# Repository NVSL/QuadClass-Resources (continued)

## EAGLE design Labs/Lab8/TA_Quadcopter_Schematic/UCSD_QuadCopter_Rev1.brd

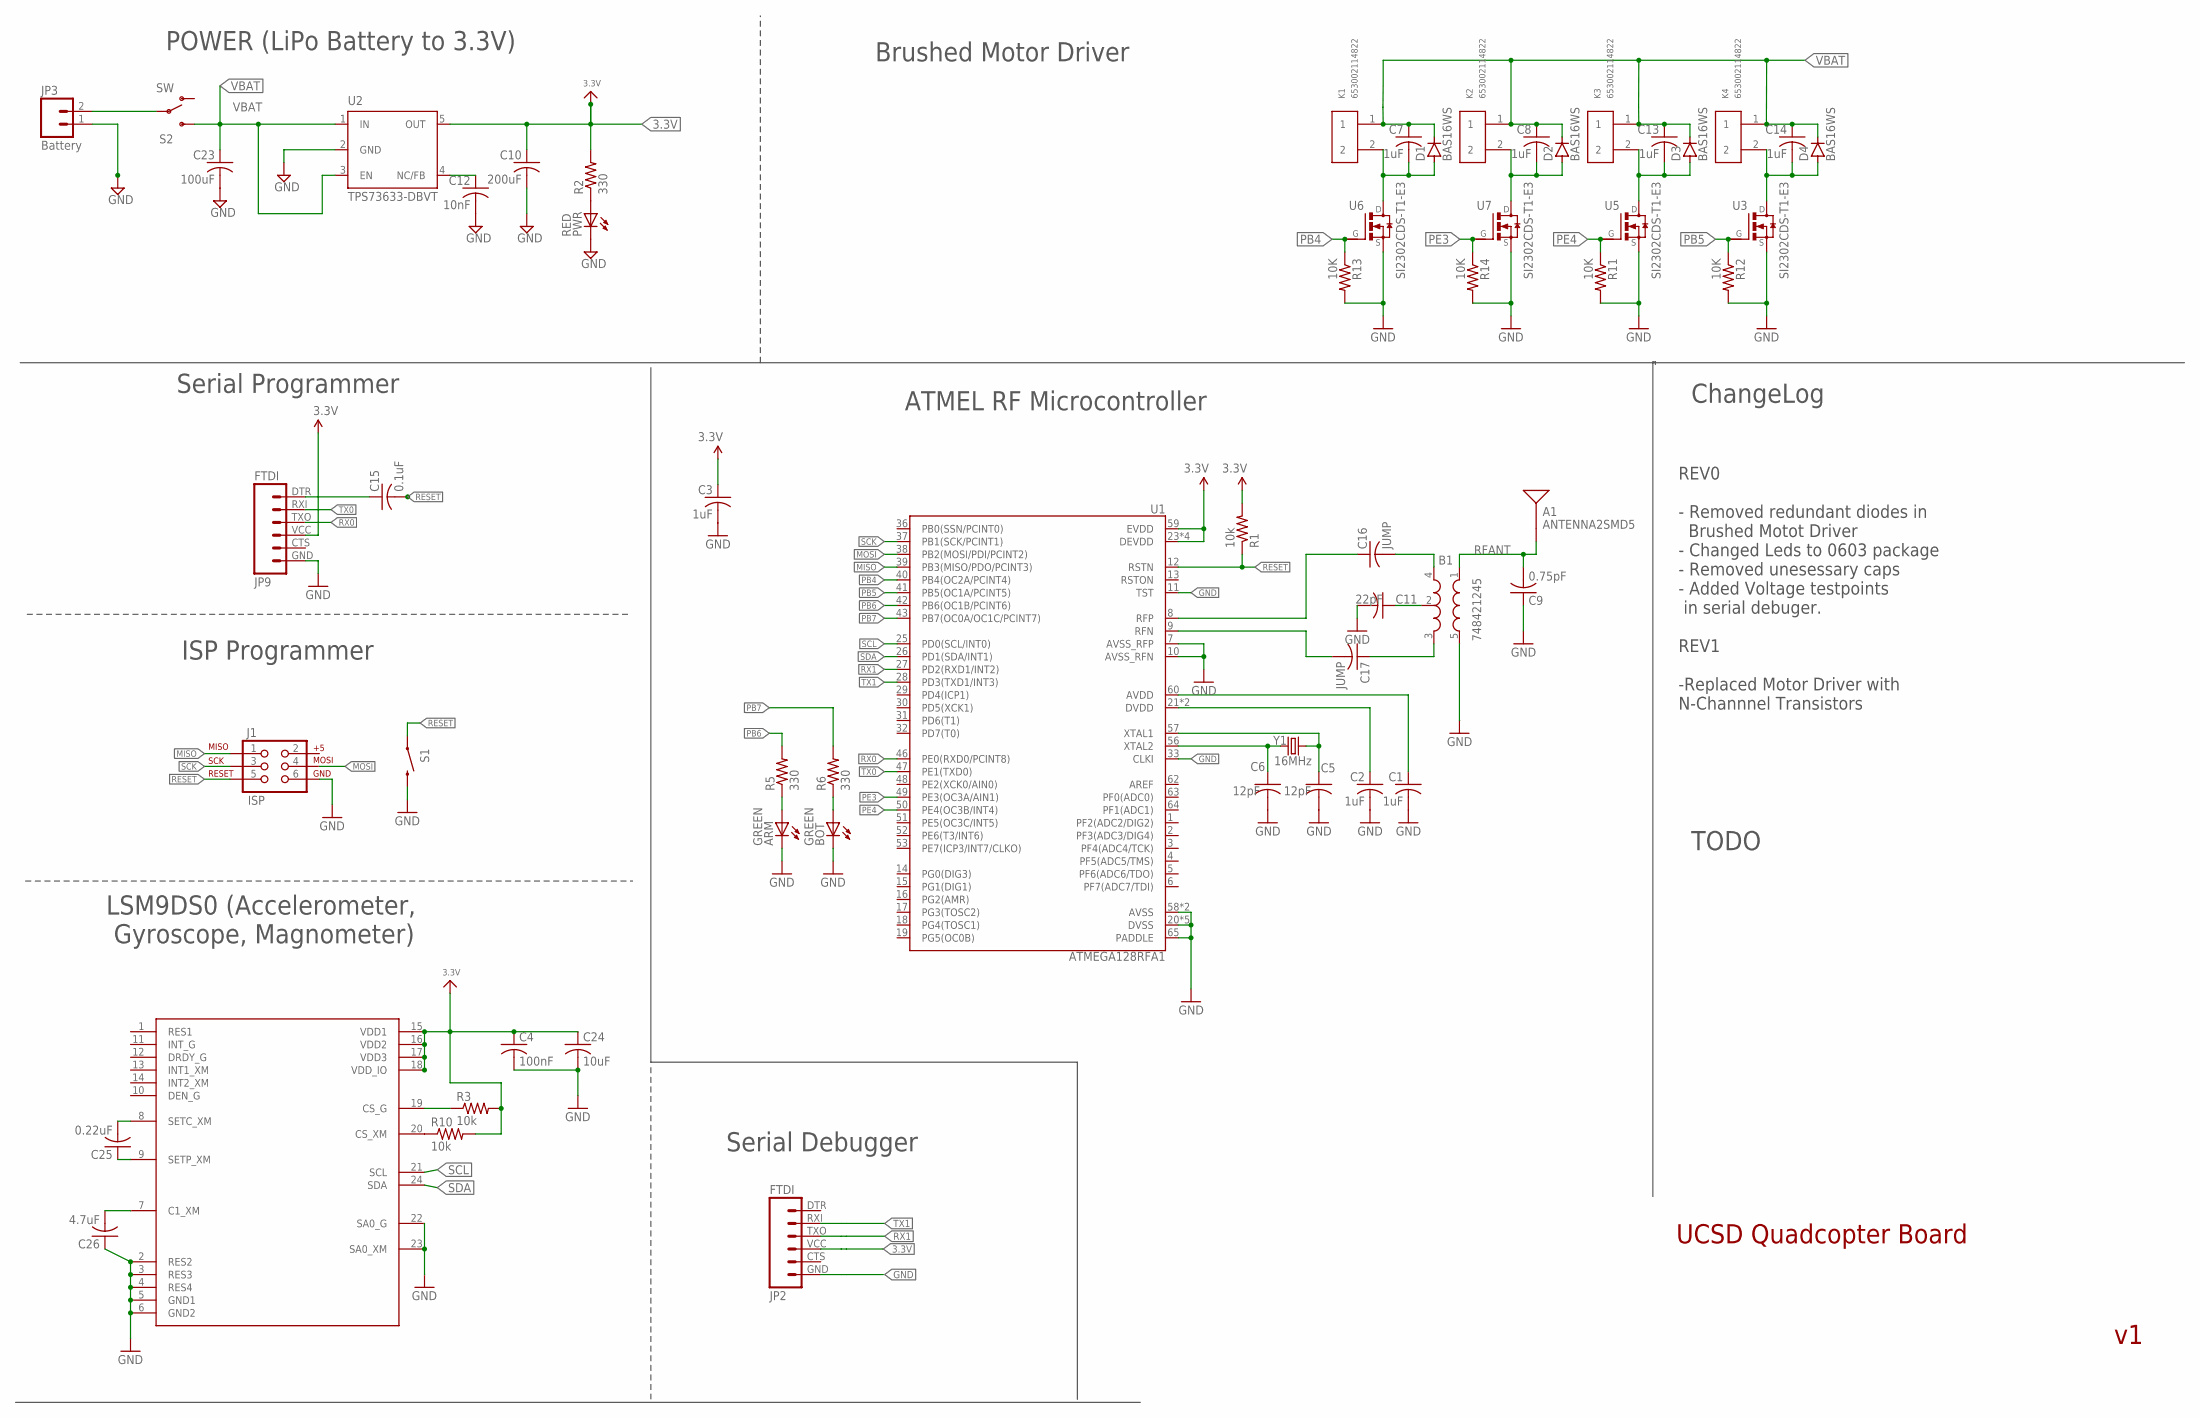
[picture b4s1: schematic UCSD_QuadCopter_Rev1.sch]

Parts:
A1: ANTENNA2SMD5; ANTENNA-CHIP5
ARM: GREEN; CHIP-LED0805
B1: 748421245; BALUN
BOT: GREEN; CHIP-LED0805
C1, C2, C3, C7, C8, C13, C14: 1uF; C0805
C4: 100nF; C0805
C5, C6: 12pF; C0805
C9: 0.75pF; C0805
C10: 200uF; C0805
C11: 22pF; C0805
C12: 10nF; C0805
C15: 0.1uF; C0805
C16, C17: JUMP; C0805
C23: 100uF; C0805
C24: 10uF; C0805
C25: 0.22uF; C0805
C26: 4.7uF; C0805
D1, D2, D3, D4: BAS16WS; SOD323_ST
J1: ISP; 2X3-NS
JP2, JP9: FTDI; FTDI_BASIC
JP3: Battery; 1X02
K1, K2, K3, K4: 653002114822
PWR: RED; CHIP-LED0805
R1, R3, R10: 10k; R0805
R2, R5, R6: 330; R0805
R11, R12, R13, R14: 10K; R0805
S1: SWITCH-MOMENTARY-2SMD; TACTILE_SWITCH_SMD
S2: SW; SWITCH-SPDT
U1: ATMEGA128RFA1; QFN-64
U2: TPS73633-DBVT; SOT23-DBV
U3, U5, U6, U7: SI2302CDS-T1-E3; SOT95P237X112-3N
U4: LSM9DS0; LGA-24
Y1: 16MHz; CRYSTAL-SMD-5X3

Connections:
3.3V: C3.1, C4.1, C10.1, C24.1, JP2.VCC (4), JP9.VCC (4), R1.2, R2.2, R3.2, R10.2, U1.23 (DEVDD), U1.34 (DEVDD), U1.44 (DEVDD), U1.54 (DEVDD), U1.59 (EVDD), U2.5 (OUT), U4.15 (VDD1), U4.16 (VDD2), U4.17 (VDD3), U4.18 (VDD_IO)
AVDD: C1.1, U1.60 (AVDD)
DTR: C15.1, JP9.DTR (1)
DVDD: C2.1, U1.21 (DVDD), U1.22 (DVDD)
GND: ARM.C, B1.5 (GND), BOT.C, C1.2, C2.2, C3.2, C4.2, C5.2, C6.2, C9.1, C10.2, C11.2, C12.2, C23.2, C24.2, C26.1, J1.6, JP2.GND (6), JP3.1, JP9.GND (6), PWR.C, R11.2, R12.2, R13.2, R14.2, S1.3 (2), U1.7 (AVSS_RFP), U1.10 (AVSS_RFN), U1.11 (TST), U1.20 (DVSS), U1.24 (DVSS), U1.33 (CLKI), U1.35 (DVSS), U1.45 (DVSS), U1.55 (DVSS), U1.58 (AVSS), U1.61 (AVSS), U1.65 (PADDLE), U2.2 (GND), U3.2 (S), U4.2 (RES2), U4.3 (RES3), U4.4 (RES4), U4.5 (GND1), U4.6 (GND2), U4.22 (SA0_G), U4.23 (SA0_XM), U5.2 (S), U6.2 (S), U7.2 (S)
MISO: J1.1, U1.39 (PB3(MISO/PDO/PCINT3))
MOSI: J1.4, U1.38 (PB2(MOSI/PDI/PCINT2))
unnamed: C12.1, U2.4 (NC/FB)
unnamed: PWR.A, R2.1
unnamed: C5.1, U1.57 (XTAL1), Y1.3 (2)
unnamed: C6.1, U1.56 (XTAL2), Y1.1
unnamed: B1.2 (GND), C11.1
unnamed: ARM.A, R5.1
unnamed: B1.4 (OUT1), C16.2
unnamed: B1.3 (OUT2), C17.1
unnamed: BOT.A, R6.1
unnamed: JP3.2, S2.2
unnamed: C26.2, U4.7 (C1_XM)
unnamed: C25.2, U4.8 (SETC_XM)
unnamed: C25.1, U4.9 (SETP_XM)
unnamed: R3.1, U4.19 (CS_G)
unnamed: R10.1, U4.20 (CS_XM)
unnamed: C7.2, D1.A, K1.2, U6.3 (D)
unnamed: C8.2, D2.A, K2.2, U7.3 (D)
unnamed: C13.2, D3.A, K3.2, U5.3 (D)
unnamed: C14.2, D4.A, K4.2, U3.3 (D)
PB4: R13.1, U1.40 (PB4(OC2A/PCINT4)), U6.1 (G)
PB5: R12.1, U1.41 (PB5(OC1A/PCINT5)), U3.1 (G)
PB6: R5.2, U1.42 (PB6(OC1B/PCINT6))
PB7: R6.2, U1.43 (PB7(OC0A/OC1C/PCINT7))
PE3: R14.1, U1.49 (PE3(OC3A/AIN1)), U7.1 (G)
PE4: R11.1, U1.50 (PE4(OC3B/INT4)), U5.1 (G)
RESET: C15.2, J1.5, R1.1, S1.1, U1.12 (RSTN)
RFANT: A1.FEED, B1.1 (IN), C9.2
RFN: C17.2, U1.9 (RFN)
RFP: C16.1, U1.8 (RFP)
RX0: JP9.TXO (3), U1.46 (PE0(RXD0/PCINT8))
RX1: JP2.TXO (3), U1.27 (PD2(RXD1/INT2))
SCK: J1.3, U1.37 (PB1(SCK/PCINT1))
SCL: U1.25 (PD0(SCL/INT0)), U4.21 (SCL)
SDA: U1.26 (PD1(SDA/INT1)), U4.24 (SDA)
TX0: JP9.RXI (2), U1.47 (PE1(TXD0))
TX1: JP2.RXI (2), U1.28 (PD3(TXD1/INT3))
VBAT: C7.1, C8.1, C13.1, C14.1, C23.1, D1.C, D2.C, D3.C, D4.C, K1.1, K2.1, K3.1, K4.1, S2.3 (S), U2.1 (IN), U2.3 (EN)

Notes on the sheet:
LSM9DS0 (Accelerometer, Gyroscope, Magnometer)
POWER (LiPo Battery to 3.3V)
Brushed Motor Driver
UCSD Quadcopter Board
Serial Programmer
ISP Programmer
Serial Debugger
ATMEL RF Microcontroller
ChangeLog
REV0 - Removed redundant diodes in Brushed Motot Driver - Changed Leds to 0603 package - Removed unesessary caps - Added Voltage testpoints in serial debuger. REV1 -Replaced Motor Driver with N-Channnel Transistors
TODO

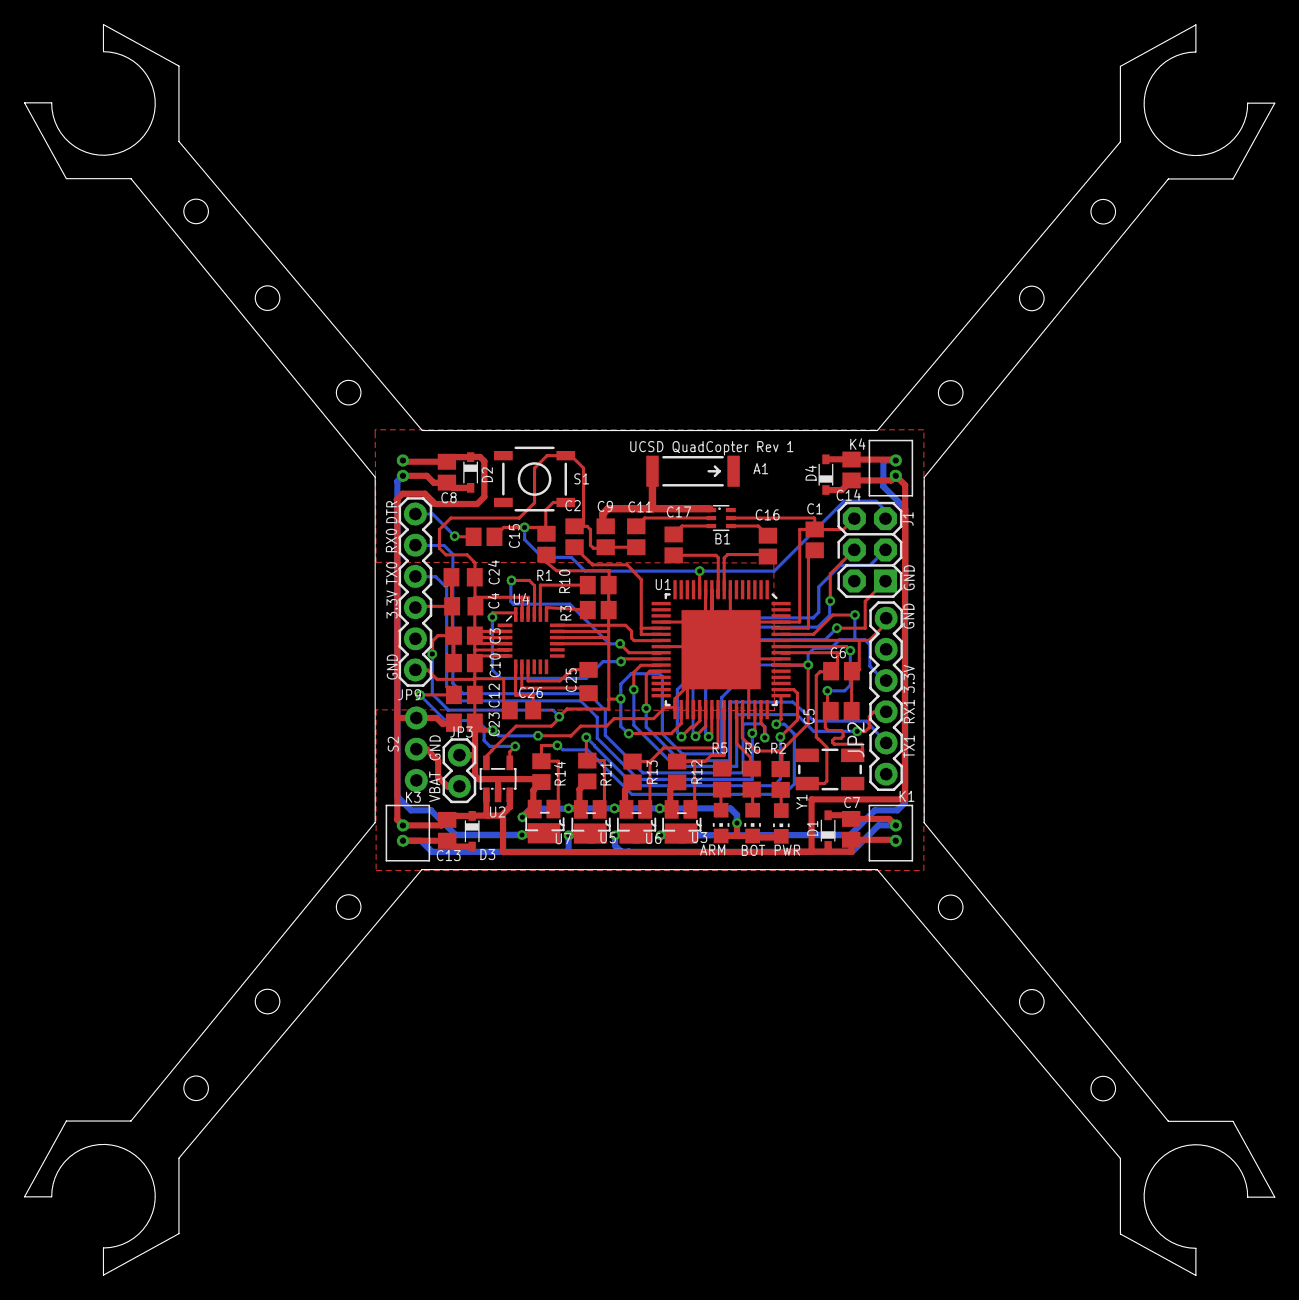
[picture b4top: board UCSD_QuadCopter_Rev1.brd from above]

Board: 2 copper layers, 101.8 x 101.9 mm, 58 parts (1 on the bottom side), 44 nets.

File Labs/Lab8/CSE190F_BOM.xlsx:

Quadcopter BOM
PART NUMBER | NAME | DESCRIPTION | Price Each
INTEGRATED CIRCUITS
ATMEGA128RFA1-ZUR00DKR-ND | ATMEGA128RFA1 | IC AVR MCU 2.4GHZ XCEIVER 64QFN | 10.31
497-13902-1-ND | LSM9DS0 | IC 3D acc; 3D gyro; 3D mag | 9.8699999999999992
LP3985IM5X-3.0/NOPBCT-ND | LP3985-3.0V | IC REG LDO 3V 0.15A SOT23-5 | 0.62
ANT-2.45-CHPCT-ND | ANTENNA | ANT 2.4GHZ 802.11 BLUETOOTH SMD | 3.16
732-2230-6-ND | BALUN Antenna Filter | BALUN EMBER351 & 357 0805 SMD | 2.63
SI2302CDS-T1-E3CT-ND | Mosfet N-Channel | MOSFET N-CH 20V 2.6A SOT-23 | 0.47
BAS16WS-E3-08CT-ND | Diode | DIODE GEN PURP 75V 250MA SOD323 | 0.23
535-9122-1-ND | Crystal | Crystal 16.0000MHz 20ppm 18pF 50 Ohm -20°C - 70°C Surface Mount 4-SMD, No Lead 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 | 1.04
LEDS
160-1412-1-ND | RED | LED RED ORANGE CLEAR 0805 SMD | 0.5
160-1887-1-ND | GREEN | LED GREEN CLEAR 0805 SMD | 0.55000000000000004
160-1887-1-ND | GREEN | LED GREEN CLEAR 0805 SMD | 0.55000000000000004
160-1416-1-ND | YELLOW | LED YELLOW CLEAR 0805 SMD | 0.37
160-1413-1-ND | ORANGE | LED YELLOW ORANGE CLEAR 0805 SMD | 0.32
160-1579-1-ND | BLUE | LED BLUE CLEAR 0805 SMD | 0.39
CAPACITORS
490-5531-1-ND | 12pF | CAP CER 12PF 250V 5% NP0 0805 | 0.28999999999999998
490-5534-1-ND | 22pF | CAP CER 22PF 250V 5% NP0 0805 | 0.28999999999999998
490-8295-1-ND | 0.01uF/10000PF | CAP CER 10000PF 50V 1% NP0 0805 | 0.65
490-1666-1-ND | 0.1uF/100nF | CAP CER 0.1UF 50V 10% X7R 0805 | 0.18
490-1670-1-ND | 0.22uF | CAP CER 0.22UF 50V 10% X7R 0805 | 0.25
1276-2702-1-ND | 0.75pF | CAP CER 0.75PF 50V NP0 0805 | 0.1
490-4736-1-ND | 1uF | CAP CER 1UF 50V 10% X7R 0805 | 0.45
490-3335-1-ND | 4.7uF | CAP CER 4.7UF 25V 10% X5R 0805 | 0.28999999999999998
490-5523-1-ND | 10uF | CAP CER 10UF 25V 10% X5R 0805 | 0.35
718-1607-1-ND | 100uF | CAP TANT 100UF 6.3V 20% 0805 | 2.0499999999999998
RESISTORS
311-10KARCT-ND | 10K Ohms | RES SMD 10K OHM 5% 1/8W 0805 | 0.1
311-270ARCT-ND | 270 Ohms | RES SMD 270 OHM 5% 1/8W 0805 | 0.1
311-680ARCT-ND | 680 Ohms | RES SMD 680 OHM 5% 1/8W 0805 | 0.1
311-100ARCT-ND | 100 Ohms | RES SMD 100 OHM 5% 1/8W 0805 | 0.1
311-30ARCT-ND | 30 Ohms | RES SMD 33 OHM 5% 1/8W 0805 | 0.1
311-0.0ARCT-ND | 0.0 Ohms | RES SMD 0.0 OHM JUMPER 1/8W 0805 | 0.1
311-330ARCT-ND | 330 Ohms | RES SMD 330 OHM 5% 1/8W 0805 | 0.1
SWITCHES
CKN9104CT-ND | Momentary Switch | SWITCH TACTILE SPST-NO 0.05A 12V | 0.65
https://www.sparkfun.com/products/9609 | Power Switch | SPDT Slide Switch | 0.75
CONECTORS
WM8344-ND | Crimp Terminal | CONN TERM MALE 24-28AWG TIN | 0.34
WM8347-ND | Plastic Connector | CONN PLUG 2POS 2MM WIRE TO WIRE | 0.37
(MOTORS, PROPELLER, BATTERY...)
http://www.amazon.com/AVAWO-Hubsan-H107C-Quadcopter-Velcro/d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 | Quad Misc | Hubsan Crash Pack | 26.99
Controller BOM
PART NUMBER | NAME | DESCRIPTION | Price Each
PARTS
CP3-1000-ND | Battery Plug | CONN 2.1MM FEMALE PLUG 5.5MM OUT | 1.36
BC4AAW-ND | AA Battery Holder | HOLDER BATT 4-AA CELLS WIRE LDS | 1.51
http://www.hobbyking.com/hobbyking/store/uh_viewItem.asp?idP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 | Gimble (L) | Gimbal Left | 4.71
http://www.hobbyking.com/hobbyking/store/uh_viewItem.asp?idP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 | Gimble (R) | Gimble Right | 4.76
https://www.sparkfun.com/products/11197 | Breakout Board | 128RFA1 board | 49.95
https://www.sparkfun.com/products/9067 | LCD | 3.3V Serial LCD | 24.95
S7005-ND | 1x7 female headers | Connector Header 7 Position 0.100" (2.54mm) Tin Through Hole | 0.78
S7006-ND | 1x8 female headers | Connector Header 8 Position 0.100" (2.54mm) Tin Through Hole | 0.86
S7004-ND | 1x6 female headers | Connector Header 6 Position 0.100" (2.54mm) Tin Through Hole | 0.68
929835E-01-36-ND | 1x6 right angle header | CONN HEADER .100 SNGL R/A 36POS | 1.88
CP-002A-ND | Barrel jack accepter | CONN POWER JACK 2.1MM | 0.93
https://www.sparkfun.com/products/11301 | USB mini cables | USB 2.0 type A to Mini-B 5-pin cable | 3.95
N107-ND | AA batteries | BATTERY IND ALKALINE AA SIZE
A100097-ND | Gimbals Connector | JST vertical (shroud) | 0.13
5.6KQBK-ND | 5.6k | Resistor | 0.1
CF14JT10K0CT-ND | 10k | Resistor | 0.1
https://www.sparkfun.com/products/9873 | Serial programmer | FTDI 3.3V Serial programer | 14.95
https://www.sparkfun.com/products/9915 | LCD Serial Connector | JST Jumper 3 Wire Assembly | 1.5

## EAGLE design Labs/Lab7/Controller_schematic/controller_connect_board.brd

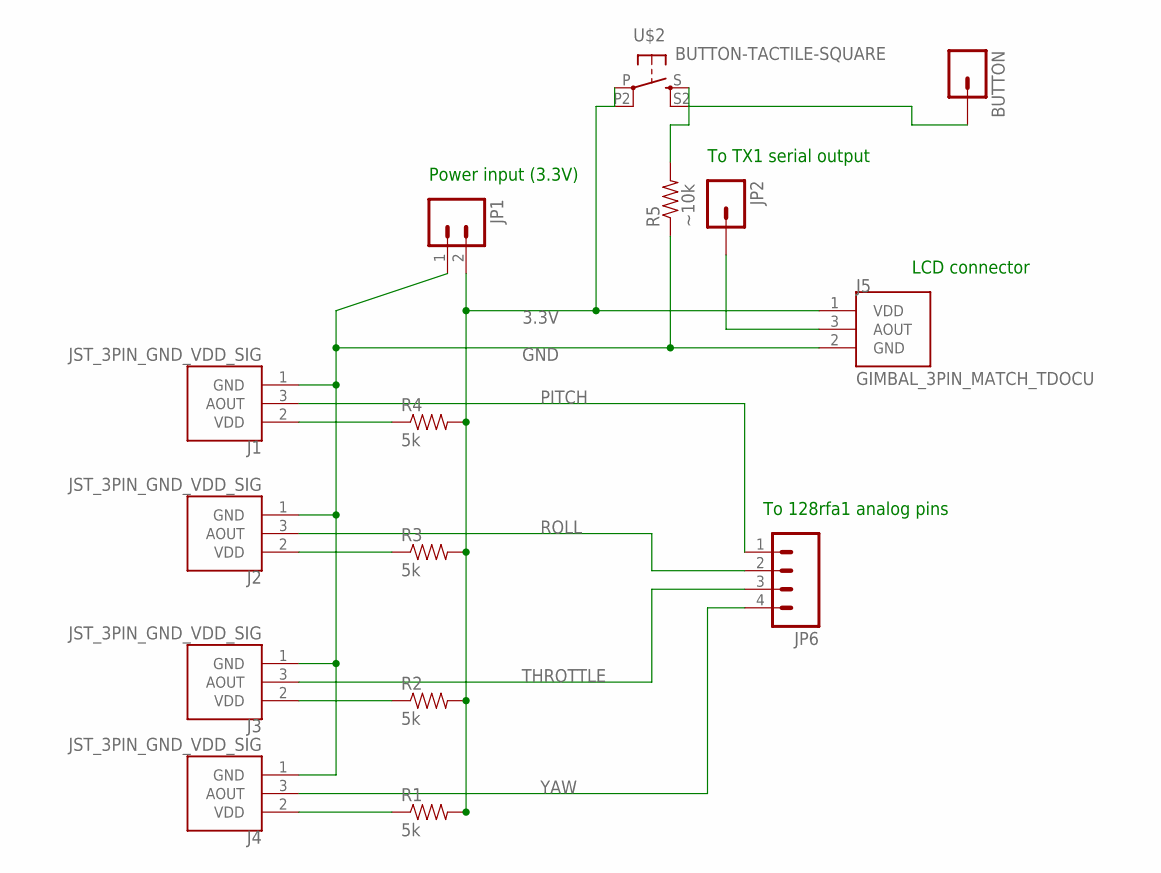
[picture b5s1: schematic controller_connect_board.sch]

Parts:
BUTTON: M01PTH; 1X01
J1, J2, J3, J4: JST_3PIN_GND_VDD_SIG; JST-3-PTH-REVERSE
J5: GIMBAL_3PIN_MATCH_TDOCU; JST-3-PTH
JP1: M021X02_NO_SILK; 1X02_NO_SILK
JP2: M01PTH; 1X01
JP6: M04PTH; 1X04
R1, R2, R3, R4: 5k; AXIAL-0.4
R5: ~10k; AXIAL-0.4
U$2: BUTTON-TACTILE-SQUARE; BUTTON-TACTILE-SQUARE-ADAFRUIT1010

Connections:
3.3V: J5.1 (VDD), JP1.2, R1.P$2 (2), R2.P$2 (2), R3.P$2 (2), R4.P$2 (2), U$2.P, U$2.P2 (P1)
GND: J1.1 (GND), J2.1 (GND), J3.1 (GND), J4.1 (GND), J5.2 (GND), JP1.1, R5.P$1 (1)
unnamed: J4.2 (VDD), R1.P$1 (1)
unnamed: J3.2 (VDD), R2.P$1 (1)
unnamed: J2.2 (VDD), R3.P$1 (1)
unnamed: J1.2 (VDD), R4.P$1 (1)
unnamed: BUTTON.1, R5.P$2 (2), U$2.S, U$2.S2 (S1)
unnamed: J5.3 (AOUT), JP2.1
PITCH: J1.3 (AOUT), JP6.1
ROLL: J2.3 (AOUT), JP6.2
THROTTLE: J3.3 (AOUT), JP6.3
YAW: J4.3 (AOUT), JP6.4

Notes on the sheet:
Power input (3.3V)
To 128rfa1 analog pins
LCD connector
To TX1 serial output

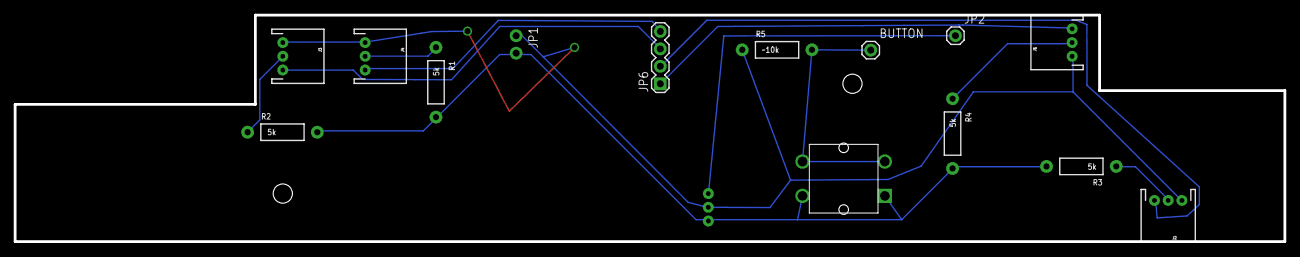
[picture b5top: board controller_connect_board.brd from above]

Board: 2 copper layers, 185.0 x 33.0 mm, 16 parts (1 on the bottom side), 12 nets.

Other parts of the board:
U$1: CONNECTOR_BOARD_OUTLINE

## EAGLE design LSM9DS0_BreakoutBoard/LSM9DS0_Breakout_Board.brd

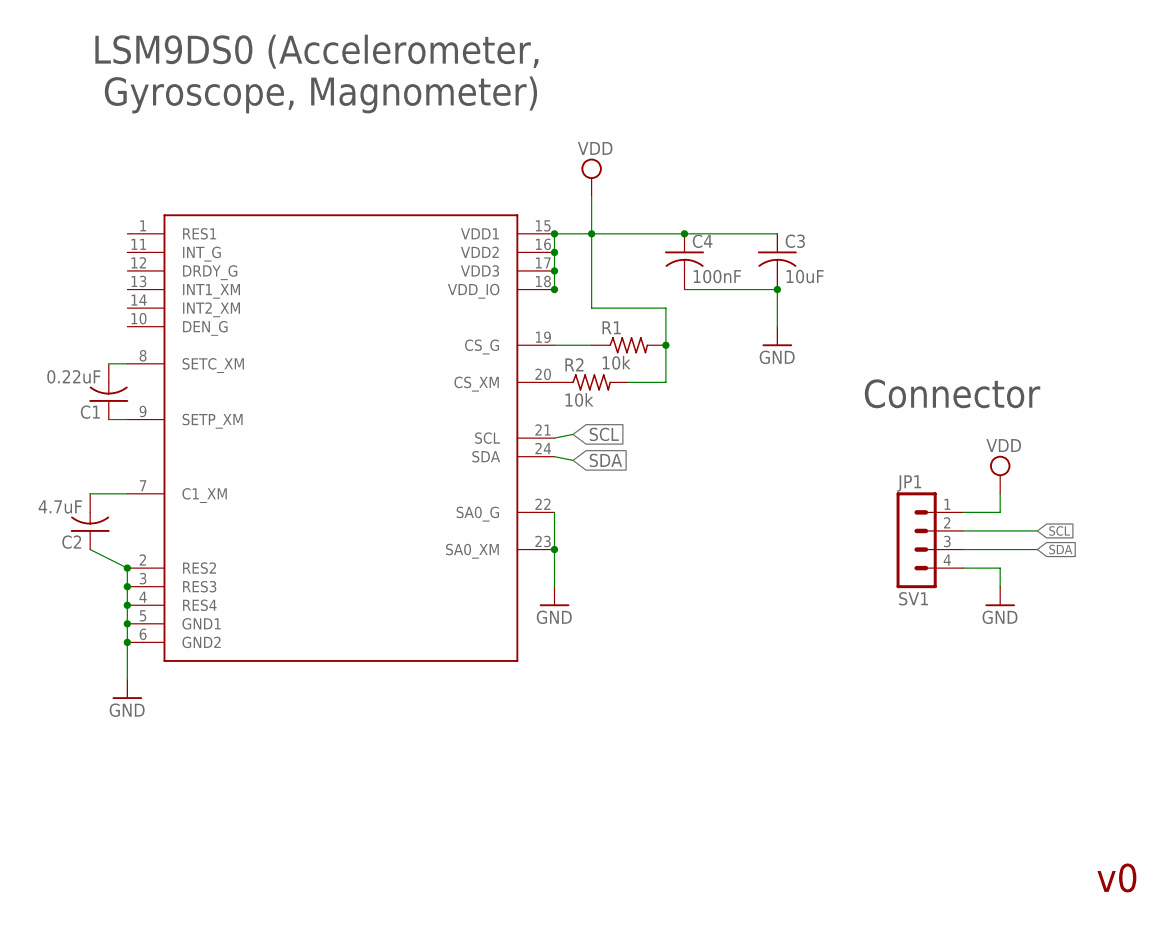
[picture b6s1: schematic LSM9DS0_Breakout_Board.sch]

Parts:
C1: 0.22uF; C0805
C2: 4.7uF; C0805
C3: 10uF; C0805
C4: 100nF; C0805
R1, R2: 10k; R0805
SV1: JP1; MA04-1
U1: LSM9DS0; LGA-24

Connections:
GND: C2.1, C3.2, C4.2, SV1.4, U1.2 (RES2), U1.3 (RES3), U1.4 (RES4), U1.5 (GND1), U1.6 (GND2), U1.22 (SA0_G), U1.23 (SA0_XM)
unnamed: C2.2, U1.7 (C1_XM)
unnamed: C1.2, U1.8 (SETC_XM)
unnamed: C1.1, U1.9 (SETP_XM)
unnamed: R1.1, U1.19 (CS_G)
unnamed: R2.1, U1.20 (CS_XM)
SCL: SV1.2, U1.21 (SCL)
SDA: SV1.3, U1.24 (SDA)
VDD: C3.1, C4.1, R1.2, R2.2, SV1.1, U1.15 (VDD1), U1.16 (VDD2), U1.17 (VDD3), U1.18 (VDD_IO)

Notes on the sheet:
LSM9DS0 (Accelerometer, Gyroscope, Magnometer)
Connector

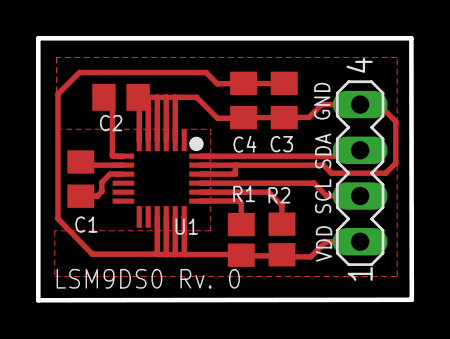
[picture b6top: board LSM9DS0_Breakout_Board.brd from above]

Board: 2 copper layers, 20.8 x 14.6 mm, 8 parts (0 on the bottom side), 9 nets.

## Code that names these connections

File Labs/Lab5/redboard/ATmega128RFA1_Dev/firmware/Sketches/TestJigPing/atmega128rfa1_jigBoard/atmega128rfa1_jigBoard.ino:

/*
  ATmega128RFA1 Dev Board On Test Jig
  by: Jim Lindblom
      SparkFun Electronics
  date: June 3, 2012
  License: Beerware. Feel free to use, reuse, and modify this code
  as you please. If you find it useful, you can buy me a beer.

  This is the code that lives on our on-test-jig ATmega128RFA1
  board. It'll wait for a button press on PE2, then send an RF
  ping out to the board to be tested. It'll then wait for a
  response. If it receives the correct response it'll light up the
  "Pass" LED on PE3.
  
  Hardware:
    PORTE2 = Button, tied to ground
    PORTE3 = LED connected through 330&ohm; to ground
*/

/* Dev board specific defines: RF RX and TX LEDs: */
#define RXLED_DDR  DDRB
#define RXLED_PORT PORTB
#define RXLED_POS  PB6

#define TXLED_DDR  DDRB
#define TXLED_PORT PORTB
#define TXLED_POS  PB7

/* Test-jig specific defines: button and LED */
#define LED_DDR  DDRE
#define LED_PORT PORTE
#define LED_POS  PE3

#define BUTTON_DDR  DDRE
#define BUTTON_PORT PORTE
#define BUTTON_PIN  PINE
#define BUTTON_POS  PE2

/* Variables for test jig state machine */
enum testPoint
{
  WAITING_BUTTON,  // Loop waiting for the test button to press
  BUTTON_PRESSED,  // Prepare to send test char
  SENDING,  // Send the test character
  WAITING_SENT,  // Busy-loop and eventually timeout after sending
  RECEIVED,  // Upon received, check if the correct char is rec'd
  RECEIVED_GOOD,  // If received good, continue testing...
};
byte testStatus = WAITING_BUTTON;
const char testSendChar = 'j';
char receivedChar = 0;

byte rssiRaw;  // Global variable to store RSSI raw reading

unsigned int timeout = 0;
const unsigned int TIMEOUT_MAX = 1000;  // timeout in miliseconds
  
void setup()
{
  ioInit();
  Serial.begin(9600);
  initRadio();
}

void loop()
{
  switch (testStatus)
  {
    case WAITING_BUTTON:
      while (!readButton())
        ;
      while (readButton())
        ;  // Wait for button to depress
      // Button pressed, prepare to test
      testStatus = BUTTON_PRESSED;
      break;
    case BUTTON_PRESSED:
      setPassLED(0);  // Turn pass LED off
      timeout=0;  // reset timeout variable
      testStatus = SENDING;
      break;
    case SENDING:
      txByte(testSendChar);
      testStatus = WAITING_SENT;
      break;
    case WAITING_SENT:
      delay(1);
      timeout++;
      if (timeout >= TIMEOUT_MAX)
      {
        Serial.println("Timeout Error. Restarting test.");
        testStatus = WAITING_BUTTON;
      }
      break;
    case RECEIVED:
      if (receivedChar == testSendChar + 1)
      {
        setPassLED(1);
        testStatus = RECEIVED_GOOD;
      }
      else
      {
        setPassLED(0);
        Serial.print("Receive error. Received: ");
        Serial.write(receivedChar);
        Serial.println();
        testStatus = WAITING_BUTTON;
      }
      break;
    case RECEIVED_GOOD:
      delay(250);
      testStatus = BUTTON_PRESSED;
      break;
  }
}

// Initialize button, pull-up resistor on it, on E2
// Initialize the LED on E3
// Initialize on-board LEDs for RF RX/TX
void ioInit()
{
  // Setup button:
  BUTTON_DDR &= ~(1<<BUTTON_POS);  // PB2 set as input
  BUTTON_PORT |= 1<<BUTTON_POS;  // Pull-up set
  
  // Setup LED:
  LED_DDR |= (1<<LED_POS);  // PB3 set as output
  setPassLED(0);
  
  // Setup RX/TX LEDs:
  TXLED_DDR |= (1<<TXLED_POS);
  TXLED_PORT &= ~(1<<TXLED_POS);
  RXLED_DDR |= (1<<RXLED_POS);
  RXLED_PORT &= ~(1<<RXLED_POS);
}

byte readButton()
{
  if (!(BUTTON_PIN & (1<<BUTTON_POS)))
    return 1;
  else
    return 0;
}

void setPassLED(byte on)
{
  if (on)
    LED_PORT |= (1<<LED_POS);
  else
    LED_PORT &= ~(1<<LED_POS);
}

void initRadio()
{
  uint8_t status;
  
  TRXPR &= ~(1<<TRXRST);  // TRX Reset Low
  TRXPR &= ~(1<<SLPTR);   // TRX SLPTR Low
  delay(1);
  TRXPR |= (1<<TRXRST);   // TRX Reset High
  
  /* disable IRQ and clear any pending IRQ's */
  IRQ_MASK = 0;  // Disable all IRQs
  TRX_STATE = (TRX_STATE & 0xE0) | TRX_OFF;  // Set to TRX_OFF state
  delay(1);  
  status = TRX_STATUS & 0x1F;  // Check to make sure state is correct
  if (status != TRX_OFF)
    Serial.println("Error, TRX isn't off");
    
  TRX_CTRL_1 |= (1<<TX_AUTO_CRC_ON);  // Enable automatic CRC calc. 
  /* Enable RX start/end and TX end interrupts */
  IRQ_MASK = (1<<RX_START_EN) | (1<<RX_END_EN) | (1<<TX_END_EN);
  PHY_CC_CCA = (PHY_CC_CCA & 0xE0) | 11; // Set the channel to 11
  TRX_STATE = (TRX_STATE & 0xE0) | RX_ON; // Default to receiver
}

void txByte(uint8_t b)
{
  uint8_t length = 3;
  
  TRX_STATE = (TRX_STATE & 0xE0) | PLL_ON;  // Set to TX start state
  while(!(TRX_STATUS & PLL_ON))
    ;  // Wait for PLL to lock
    
  TXLED_PORT |= (1<<TXLED_POS);  // Turn on TX LED
  
  TRXFBST = length;
  memcpy((void *)(&TRXFBST+1), &b, 1);
  
  TRXPR |= (1<<SLPTR);   // SLPTR high
  TRXPR &= ~(1<<SLPTR);  // SLPTR low
  
  TRX_STATE = (TRX_STATE & 0xE0) | RX_ON;
}

// Transmit End ISR
ISR(TRX24_TX_END_vect)
{
  TXLED_PORT &= ~(1<<TXLED_POS);  // Turn off TX LED
}
// Receive END ISR
ISR(TRX24_RX_END_vect)
{
  uint8_t length;
  uint8_t tempFrame[127];
  
  if (rssiRaw & RX_CRC_VALID)
  {
    length = TST_RX_LENGTH;
    memcpy(&tempFrame[0], (void*)&TRXFBST, length);
  }
  receivedChar = tempFrame[0];
  testStatus = RECEIVED;
  
  RXLED_PORT &= ~(1<<RXLED_POS);  // Turn off RX LED
}

// Receive Start ISR
ISR(TRX24_RX_START_vect)
{
  RXLED_PORT |= (1<<RXLED_POS);  // Turn on RX LED
  rssiRaw = PHY_RSSI;
}

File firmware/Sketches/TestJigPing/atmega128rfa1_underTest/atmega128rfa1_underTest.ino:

/*
  ATmega128RFA1 Dev Board Under Test Jig
  by: Jim Lindblom
      SparkFun Electronics
  date: June 3, 2012
  License: Beerware. Feel free to use, reuse, and modify this code
  as you please. If you find it useful, you can buy me a beer.

  This is the code that lives on the ATmega128RFA1 under test.
  It'll wait to receive a test character sent over RF. Once
  received, it'll test its I/O pins. If the pin-test passes, it'll
  increment the value of the character by one (e.g. 'j' becomes 'k')
  and send that back over RF. Once received by the on-jig 128RFA1
  board, the pass LED should light up!
  
  Hardware:
    The ATmega128RFA1 Dev Board should do a self test.
    All I/O pins are tied to one of two nets (alternating based
    on their chip position).

 NET 1: B4, D1, D3, D5, D7, E3, E5, E7, G1, G5, F1, F3, F5, F7
 NET 2: B0, B5, D0, D2, D4, D6, E2, E4, E6, G0, G2, F0, F2, F4, F6
*/

/* Dev board specific defines: RF RX and TX LEDs: */
#define RXLED_DDR  DDRB
#define RXLED_PORT PORTB
#define RXLED_POS  PB6

#define TXLED_DDR  DDRB
#define TXLED_PORT PORTB
#define TXLED_POS  PB7  

/* Variables for test jig state machine */
enum testPoint
{
  WAITING_RX,
  TESTING_IO
};
byte testStatus = WAITING_RX;
char receivedChar = 0;

byte rssiRaw;  // Global variable to store RSSI raw reading

void setup()
{
  ioInit();
  Serial.begin(9600);
  initRadio();
}

void loop()
{
  switch (testStatus)
  {
    case WAITING_RX:
      delay(1);
      break;
    case TESTING_IO:
      if (testIO() == 2)
      {
        txByte(++receivedChar);
      }
      else
      {
        txByte(0);
      }
      testStatus = WAITING_RX;
      break;
  }
}

// Initialize on-board LEDs for RF RX/TX
// Initialize nets as both inputs
void ioInit(void)
{  
  // Setup RX/TX LEDs:
  TXLED_DDR |= (1<<TXLED_POS);
  TXLED_PORT &= ~(1<<TXLED_POS);
  RXLED_DDR |= (1<<RXLED_POS);
  RXLED_PORT &= ~(1<<RXLED_POS);
  
  testIoInit();
}

void testIoInit(void)
{
  // Setup all but first net pins as inputs, no pull-up
  
  DDRB &= 0b11001110;
  DDRD &= 0b00000000;
  DDRE &= 0b00000011;
  DDRF &= 0b00000000;
  DDRG &= 0b11011000;
  
  PORTB &= 0b11001110;
  PORTD &= 0b00000000;
  PORTE &= 0b00000011;
  PORTF &= 0b00000000;
  PORTG &= 0b11011000;
}

uint8_t testIO(void)
{
  uint8_t testPass = 0;
  
  testIoInit();
  
  // Part 1: Set Net 1 high, read all pins
  DDRB |= (1<<PB4);  // Set first pin high
  PORTB |= (1<<PB4);
  DDRB |= (1<<PB0);  // Set first pin high
  PORTB &= ~(1<<PB0);
  delay(1);
  Serial.println(PIND&0xFF, HEX);
  Serial.println(PINE&0xFC, HEX);
  Serial.println(PINF&0xFF, HEX);
  Serial.println(PING&0x27, HEX);
  Serial.println("---");
  if ( ((PIND & 0xFF)==0xAA) && ((PINE & 0xFC)==0xA8) &&
       ((PINF & 0xFF)==0xAA) && ((PING & 0x27)==0x22) )
  {
    testPass++;
  }
  Serial.println(testPass);
  
  testIoInit();
  // Part 2: Set Net 2 high, read all pins
  DDRB |= (1<<PB0);  // Set first pin high
  PORTB |= (1<<PB0);
  DDRB |= (1<<PB4);  // Set first pin high
  PORTB &= ~(1<<PB4);
  delay(1);
  Serial.println(PINB&0x31, HEX);
  Serial.println(PIND&0xFF, HEX);
  Serial.println(PINE&0xFC, HEX);
  Serial.println(PINF&0xFF, HEX);
  Serial.println(PING&0x27, HEX);
  Serial.println("---");
  if ( ((PINB & 0x31)==0x21) && 
       ((PIND & 0xFF)==0x55) && ((PINE & 0xFC)==0x54) && 
       ((PINF & 0xFF)==0x55) && ((PING & 0x27)==0x05) )
  {
    testPass++;
  }
  Serial.println(testPass);
  
  return testPass;
}

void initRadio(void)
{
  uint8_t status;
  
  TRXPR &= ~(1<<TRXRST);  // TRX Reset Low
  TRXPR &= ~(1<<SLPTR);   // TRX SLPTR Low
  delay(1);
  TRXPR |= (1<<TRXRST);   // TRX Reset High
  
  /* disable IRQ and clear any pending IRQ's */
  IRQ_MASK = 0;  // Disable all IRQs
  TRX_STATE = (TRX_STATE & 0xE0) | TRX_OFF;  // Set to TRX_OFF state
  delay(1);  
  status = TRX_STATUS & 0x1F;  // Check to make sure state is correct
  if (status != TRX_OFF)
    Serial.println("Error, TRX isn't off");
    
  TRX_CTRL_1 |= (1<<TX_AUTO_CRC_ON);  // Enable automatic CRC calc. 
  /* Enable RX start/end and TX end interrupts */
  IRQ_MASK = (1<<RX_START_EN) | (1<<RX_END_EN) | (1<<TX_END_EN);
  PHY_CC_CCA = (PHY_CC_CCA & 0xE0) | 11; // Set the channel to 11
  TRX_STATE = (TRX_STATE & 0xE0) | RX_ON; // Default to receiver
}

void txByte(uint8_t b)
{
  uint8_t length = 3;
  
  TRX_STATE = (TRX_STATE & 0xE0) | PLL_ON;  // Set to TX start state
  while(!(TRX_STATUS & PLL_ON))
    ;  // Wait for PLL to lock
    
  TXLED_PORT |= (1<<TXLED_POS);  // Turn on TX LED
  
  TRXFBST = length;
  memcpy((void *)(&TRXFBST+1), &b, 1);
  
  TRXPR |= (1<<SLPTR);   // SLPTR high
  TRXPR &= ~(1<<SLPTR);  // SLPTR low
  
  TRX_STATE = (TRX_STATE & 0xE0) | RX_ON;
}

// Transmit End ISR
ISR(TRX24_TX_END_vect)
{
  TXLED_PORT &= ~(1<<TXLED_POS);  // Turn off TX LED
}
// Receive END ISR
ISR(TRX24_RX_END_vect)
{
  uint8_t length;
  uint8_t tempFrame[127];
  
  if (rssiRaw & RX_CRC_VALID)
  {
    length = TST_RX_LENGTH;
    memcpy(&tempFrame[0], (void*)&TRXFBST, length);
  }
  receivedChar = tempFrame[0];
  
  testStatus = TESTING_IO;
  RXLED_PORT &= ~(1<<RXLED_POS);  // Turn off RX LED
}

// Receive Start ISR
ISR(TRX24_RX_START_vect)
{
  RXLED_PORT |= (1<<RXLED_POS);  // Turn on RX LED
  rssiRaw = PHY_RSSI;
}

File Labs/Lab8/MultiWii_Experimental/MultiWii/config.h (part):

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      //#define ADCACC

      /* enforce your individual sensor orientation - even overrides board specific defaults */
      #define FORCE_ACC_ORIENTATION(X, Y, Z)  {imu.accADC[ROLL]  = -X; imu.accADC[PITCH]  = -Y; imu.accADC[YAW]  = Z;}
      #define FORCE_GYRO_ORIENTATION(X, Y, Z) {imu.gyroADC[PITCH] = -X; imu.gyroADC[ROLL] = Y; imu.gyroADC[YAW] = -Z;}
      #define FORCE_MAG_ORIENTATION(X, Y, Z)  {imu.magADC[ROLL]  =  -X; imu.magADC[PITCH]  =  -Y; imu.magADC[YAW]  = Z;}

      /* Board orientation shift */
      /* If you have frame designed only for + mode and you cannot rotate FC phisycally for flying in X mode (or vice versa)
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
    /* NEW: not used anymore for servo coptertypes  <== NEEDS FIXING - MOVE TO WIKI */
    #define YAW_DIRECTION 1
    //#define YAW_DIRECTION -1 // if you want to reverse the yaw correction direction

    #define ONLYARMWHENFLAT //prevent the copter from arming when the copter is tilted

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    #define CAM_TIME_HIGH 1000   // the duration of HIGH state servo expressed in ms

  /***********************          Airplane                       ***********************/
    //#define USE_THROTTLESERVO // For use of standard 50Hz servo on throttle.

    //#define FLAPPERONS    AUX4          // Mix Flaps with Aileroins.
    #define FLAPPERON_EP   { 1500, 1700 } // Endpooints for flaps on a 2 way switch else set {1020,2000} and program in radio.
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     * (the throttle curve must leave room for the governor, so 0-50-75-80-80 is ok, 0-50-95-100-100 is _not_ ok.
     * Can be toggled via aux switch.
     */
    //#define GOVERNOR_P 7     // (*) proportional factor. Higher value -> higher throttle increase. Must be >=1; 0 = turn off
    //#define GOVERNOR_D 4     // (*) decay timing. Higher value -> takes longer to return throttle to normal. Must be >=1;

    //#define VOLTAGEDROP_COMPENSATION // voltage impact correction

  /***********************          Heli                           ***********************/
    /* Channel to control CollectivePitch */
    #define COLLECTIVE_PITCH      THROTTLE

    /* Limit the range of Collective Pitch. 100% is Full Range each way and position for Zero Pitch */
    #define COLLECTIVE_RANGE { 80, 0, 80 }// {Min%, ZeroPitch offset from 1500, Max%}.
    #define YAWMOTOR                 0       // If a motor is used as YAW Set to 1 else set to 0.

    /* Servo mixing for heli 120
                         {Coll,Nick,Roll} */
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    #define SERVO_RIGHT  { +10, +5, -10 } 

    /* Limit Maximum controll for Roll & Nick  in 0-100% */
    #define CONTROL_RANGE   { 100, 100 }      //  { ROLL,PITCH }

    /* use servo code to drive the throttle output. You want this for analog servo driving the throttle on IC engines.
       if inactive, throttle output will be treated as a motor output, so it can drive an ESC */
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    /****************************    PPM Sum Reciver    ***********************************/
      /* The following lines apply only for specific receiver with only one PPM sum signal, on digital PIN 2
         Select the right line depending on your radio brand. Feel free to modify the order in your PPM order is different */
      //#define SERIAL_SUM_PPM         PITCH,YAW,THROTTLE,ROLL,AUX1,AUX2,AUX3,AUX4,8,9,10,11 //For Graupner/Spektrum
      //#define SERIAL_SUM_PPM         ROLL,PITCH,THROTTLE,YAW,AUX1,AUX2,AUX3,AUX4,8,9,10,11 //For Robe/Hitec/Futaba
      //#define SERIAL_SUM_PPM         ROLL,PITCH,YAW,THROTTLE,AUX1,AUX2,AUX3,AUX4,8,9,10,11 //For Multiplex
      //#define SERIAL_SUM_PPM         PITCH,ROLL,THROTTLE,YAW,AUX1,AUX2,AUX3,AUX4,8,9,10,11 //For some Hitec/Sanwa/Others

      // Uncommenting following line allow to connect PPM_SUM receiver to standard THROTTLE PIN on MEGA boards (eg. A8 in CRIUS AIO)
      //#define PPM_ON_THROTTLE

    /**********************    Spektrum Satellite Reciver    *******************************/
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      /* AUX2 pin on pin RXO */
      //#define RCAUX2PINRXO

      /* aux2 pin on pin D17 (RXLED) */
      //#define RCAUX2PIND17

    /**********************************    Buzzer Pin    **********************************/
      /* this moves the Buzzer pin from TXO to D8 for use with ppm sum or spectrum sat. RX (not needed if A32U4ALLPINS is active) */
      //#define D8BUZZER

    /***********************      Promicro version related     ****************************/
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      /* GYRO_SMOOTHING. In case you cannot reduce vibrations _and_ _after_ you have tried the low pass filter options, you
         may try this gyro smoothing via averaging. Not suitable for multicopters!
         Good results for helicopter, airplanes and flying wings (foamies) with lots of vibrations.*/
      //#define GYRO_SMOOTHING {20, 20, 3}    // (*) separate averaging ranges for roll, pitch, yaw

    /************************    Moving Average Gyros    **********************************/
      //#define MMGYRO 10                      // (*) Active Moving Average Function for Gyros
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    #define FAILSAFE                                // uncomment  to activate the failsafe function
    #define FAILSAFE_DELAY     10                    // Guard time for failsafe activation after signal lost. 1 step = 0.1sec - 1sec in example
    #define FAILSAFE_OFF_DELAY 30                    // Time for Landing before motors stop in 0.1sec. 1 step = 0.1sec - 3sec in example
    #define FAILSAFE_THROTTLE  (MINTHROTTLE + 100)    // (*) Throttle level used for landing - may be relative to MINTHROTTLE - as in this case
    
    #define FAILSAFE_DETECT_TRESHOLD  985

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    /* defines the neutral zone of throttle stick during altitude hold, default setting is
       +/-50 uncommend and change the value below if you want to change it. */
    #define ALT_HOLD_THROTTLE_NEUTRAL_ZONE    50
    //#define ALT_HOLD_THROTTLE_MIDPOINT        1500  // in us    - if uncommented, this value is used in ALT_HOLD for throttle stick middle point instead of initialThrottleHold parameter.


    /* uncomment to disable the altitude hold feature.
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  /**************************************************************************************/
  /***********************     motor, servo and other presets     ***********************/
  /**************************************************************************************/
    /* motors will not spin when the throttle command is in low position
       this is an alternative method to stop immediately the motors */
    //#define MOTOR_STOP

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    
  /***********************             HW PWM Servos             ***********************/ 
    /* HW PWM Servo outputs for Arduino Mega.. moves:
      Pitch   = pin 44
      Roll    = pin 45
      CamTrig = pin 46
      SERVO4  = pin 11 (aileron left for fixed wing or TRI YAW SERVO)
      SERVO5  = pin 12 (aileron right for fixed wing)
      SERVO6  = pin 6   (rudder for fixed wing)
      SERVO7  = pin 7   (elevator for fixed wing)
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     * motor[0] = motor       = pin  6
     * servo[3] = nick  servo = pin 11
     * servo[4] = left  servo = pin 10
     * servo[5] = yaw   servo = pin  5
     * servo[6]  = right servo= pin  9
     */
    //#define A32U4_4_HW_PWM_SERVOS

    #define SERVO_RFR_RATE  50    // In Hz, you can set it from 20 to 400Hz, used only in HW PWM mode for mega and 32u4
    //#define SERVO_PIN5_RFR_RATE  200    // separate yaw pwm rate.
                                          // In Hz, you can set it from 20 to 400Hz, used only in HW PWM mode for 32u4


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
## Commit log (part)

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2019-03-29 Making the schematic changes
2019-03-29 only one LED is available
2019-03-29 changes for the current EAGLE CAD
2019-03-29 updated for new EAGLE CAD version
2019-03-30 Revising/polishing labs
2019-03-30 more ignoring
2019-03-30 lab starter repo improvements
2019-04-01 pdf versions of part lables for BBB
2019-04-01 use correct starter repo for eagle intro lab
2019-04-01 update labs and slides
2019-04-02 fix starter repo
2019-04-02 Fix typo in directory
2019-04-03 add serLCD library
2019-04-03 clarify about paths
2019-04-03 remove freedfm
2019-04-03 fix cam names
2019-04-04 updates for eagle parts lab
2019-04-06 Lots of updates
2019-04-06 Restore accidentally deleted text
2019-04-07 add assembly photos for remote
2019-04-07 pass eaglint
2019-04-07 clarification pass
2019-04-07 clarifaction pass. test frame part list
2019-04-08 hide old slides
2019-04-08 Refinements to lab
2019-04-08 pass new checks
2019-04-08 fix images. missing file
2019-04-08 missing parts
2019-04-08 new slides
2019-04-09 bunch of fixes
2019-04-09 add note about tcream on mesfet
2019-04-09 chip resistor mounting datasheet
2019-04-09 new photos for assembly
2019-04-09 fetch up stream instructions
2019-04-09 Fix typo
2019-04-10 Clarify parts of the IMU part spec. New DRC rules for solder mask
2019-04-10 exceptions for new tests
2019-04-10 clarify about IMU SMD width
2019-04-10 clarifications
2019-04-15 update slides and todos
2019-04-15 update slides and labs
2019-04-16 a few notes in sensing lab
2019-04-16 update slides and lab writes
2019-04-18 fix file name
2019-04-18 new slides. Lots of tweaks to layout lab
2019-04-18 missing image
2019-04-19 Tips and tricks
2019-04-19 clarifications, details, and more tips and tricks
2019-04-19 tips for PID
2019-04-21 Get rid of VIN and the associated diode. Connect 3v3 to FTDI. Don't connect ISP to 3v3.
2019-04-25 clarify
2019-04-28 PID updates
2019-04-28 Design review comments
2019-04-30 tips and tricks; clarifications
2019-04-30 cleanup 2-pin header
2019-05-01 update makefile and lab write ups
2019-05-02 clarifications for tape out
2019-05-02 remove stencil label for layer labels
2019-05-02 add board outline to top silkscreen
2019-05-02 new labels
2019-05-03 update IMU pad guidance to account for trace spacing
2019-05-05 small tweak to cam file. More detail about routing
2019-05-05 make file improvements. Especially for cam processing
2019-05-07 More about PID
2019-05-08 cleanup and write up for quadcopter assembly
2019-05-08 note about assembly drawings
2019-05-09 Surface mount FTDI and battery terminals
2019-05-09 update about building your own remote
2019-05-15 improved PID writeup
2019-05-18 include bom in release. Order 5 sets of parts by default
2019-05-18 notes on assembly
2019-05-18 comments on implementing PID
2019-05-22 Updates to flight and PID labs
2019-05-28 updated labs
2019-05-28 lab updates
2019-05-28 Trim information
2019-06-06 updated flight and PID labs
2019-06-11 new parts. Notes on cleanup
2019-06-12 TA task list updated
2019-07-07 more resistor packs
2019-10-04 mfr data for assembly house
2019-10-30 remind them to plug in their board.
2020-02-12 new parts
2020-03-12 update arduino version
2020-03-12 Some edits and fixmes.
2020-12-09 Changes for COVID.
2020-12-09 First round of edits for wi21
2020-12-09 new photos
2020-12-09 link in new photos
2020-12-09 reduce size
2020-12-09 next batch of edits for 2021
2020-12-09 Completed pass through Programming Hardware Lab
2020-12-21 pcbcart cam file
2020-12-30 Update github classroom assignment link
2020-12-30 update self-eval link.
2021-01-02 Update with new google classroom link.
2021-01-02 Clarifications.
2021-01-02 Refinements.
2021-01-02 bad schematic example
2021-01-02 Typo
2021-01-02 Programming header instructions.
2021-01-05 remove stuff about keeping remote.
2021-01-06 Many updates for 2021
2021-01-06 use pcbcart instead jlpcb
2021-01-07 add view mate
2021-01-07 add note about file name in image
2021-01-07 update grading policy.
2021-01-08 Remove reference to existing custom.lbr.
2021-01-08 update urls for libs.
2021-01-09 require eaglint teams before accepting assignmen.t
2021-01-09 clarify parts lab
2021-01-12 add note about polarity in the LED package.
2021-01-12 add some notes about the IMU schematic symbol.
2021-01-13 update checklist.
2021-01-13 update slides
2021-01-13 updates to schematic and board labs
2021-01-13 Add guidance to use max width for pads.
2021-01-13 Add clarification about trestrict between pads.
2021-01-14 Add guidance about not including reference designators in courtyards.
2021-01-14 updates for schematic lab
2021-01-16 Clarify diode selection and I2C address configuration.
2021-01-19 add note about tkeepout and tplace in the net bridge.
2021-01-20 update guidance about custom.lbr.
2021-01-20 Note about handling starter repo next time.
2021-01-20 Note about starte repor for next time.
2021-01-20 Update guidance about rescue header.
2021-01-20 updated guidance for LED documentation.
2021-01-21 updated slides
2021-01-25 Small tweaks to quadparts_prebuilt.lbr. added missing dru
2021-01-25 clarification about cap placement.
2021-01-25 Clarification on grid rules.
2021-01-26 Clarify high-current trace length requirements.
2021-01-26 Add note about layer labels.
2021-01-26 fix typo about MCU deocupling cap placement.
2021-01-26 fix font sizes
2021-01-28 improved tkeepout for battery
2021-01-28 Clarify about knobs and button example.
2021-01-29 clockwise and counter-clockwise symbols
2021-01-29 updates after lecture
2021-02-01 Add important note about rfFlush()
2021-02-02 Added video about changing motor polarity.
2021-02-04 ADd guidance about having your pours cut in half. Update guidance about pour widths.
2021-02-04 script to upload hex files
2021-02-06 updates to lab write ups and slides
2021-02-11 add notes about knots.
2021-02-12 Update rubric for yaw.
2021-02-12 Photo of quadcopter hanging upside down.
2021-02-12 Moved trimming to this lab. Updated rubric to match.
2021-02-12 Trim for 2021
2021-02-13 Framework for new rubric.
2021-02-13 Partial rubric
2021-02-18 slides update
2021-02-18 fix errors
2021-02-18 updates for pcbcart.
2021-02-18 Set goals for flight lab.
2021-03-04 Added note about the radio blinking an led.
2021-12-31 2022 updates part 1
2021-12-31 minor error in image
2021-12-31 unknown changes from long ago. And some initial updates for wi2022
2021-12-31 small tweaks
2021-12-31 2022 updates part 2
2021-12-31 small typo
2021-12-31 elaboration on F360 differences
2022-01-01 tweaks
2022-01-01 update on packages
2022-01-04 small updates
2022-01-05 wording update
2022-01-05 updates for part 4
2022-01-05 updates for 2022
2022-01-05 period
2022-01-06 Artwork Update
2022-01-06 clarification
2022-01-06 update slides, library, and add starter repo for lab 2
2022-01-06 0.9 mm for font
2022-01-07 update starter repo link.
2022-01-09 added logos etc. to make reference design work in the cloud
2022-01-09 update schematic lsab
2022-01-10 update schematic lab
2022-01-10 update board layout lab
2022-01-10 reorder some sections
2022-01-11 updates to quadcopter layout
2022-01-13 update link
2022-01-15 Fix typos
2022-01-15 Rename `SCA` to `SDA`
2022-01-15 Remove the option to connect LEDs directly to the battery
    We discussed in class recently that since our quadcopter will include a
    power switch, we should not hook up LEDs directly to the battery since
    then they drain the battery.
2022-01-19 newer version of library
2022-01-20 clarify programming header capacitor.
2022-01-20 Don't connect power on ISP.
2022-01-20 remove led_notes.txt
2022-01-20 use correct battery device.
2022-02-05 slides updates an restore missing page of IMU datasheet
2022-02-09 move battery meter to this lab.
2022-02-11 adjust guidance about driving LEDs.
2022-02-11 small updates.
2022-02-15 just one debug header.
2022-03-08 Fixed Table in Assembling PCB
2022-03-09 Update for initialization error
2023-01-20 Adding screw termminal block orientation
2023-01-20 Adding stencil bottom cam
2023-03-20 Remove COVID stuff.
2023-03-20 notes on lab 2
2023-03-21 Updating Envision Link
2023-03-21 Update tutorial for Fusion 360 update
2023-03-21 Adding grid information
2023-03-21 More helpful images and updatink datasheet link
2023-03-22 Improving Part 3
2023-03-23 Fixing Part 4, Making a SMD Component.
2023-03-23 FIx CAM and DRU Paths
2023-03-23 Fix grammar.
2023-03-25 Multiple edits
2023-03-29 Change CAM file
2023-03-29 Ignoring vscode folder
2023-03-29 Adding Windows to Grid Snap trick
2023-03-29 Adding datasheet docs for new IMU
2023-03-30 fix some typos in lab 3
2023-04-03 Update Excel link and Lab 2 link
2023-04-03 Fix varian name dash and artwork in smd.brd
2023-04-03 Fix course home page outdated link
2023-04-04 Adding LSM6DSOX IMU Notes and Footprint guide.
2023-04-05 fix file name.
2023-04-05 Adding Symbol centering note
2023-04-05 slides
2023-04-06 clarify restricts.
2023-04-08 Update for new IMU
2023-04-09 Adding battery, LEDs, New IMU, New Arduino
2023-04-10 Note on IMU footprint
2023-04-10 new assignment
2023-04-11 Remove Missing Libraries TODO
2023-04-12 Replacing 2V5 to 3V, adding 3V symbol
2023-04-12 Update IMU section for LSM6DSOX
2023-04-12 Fix IMU git
2023-04-12 Add missing Adafruit LSM6DS library
2023-04-12 Fix spelling
2023-04-14 allow sot23 for package generation
2023-04-14 images for battery sensing
2023-04-14 battery sensing exercise
2023-04-14 remove github classroom link
2023-04-14 Indicate where is quadparts_prebuilt_2022
2023-04-17 Update sensing and filter for new IMU
2023-04-17 Add missing constants link for IMU
2023-04-18 fix battery component.
2023-04-18 Adding LEDs pinout
2023-04-18 Updates for PCB layout.
2023-04-19 Add free PWM pins
2023-04-19 Add a note on 3V3 vs 3V.
2023-04-19 2V5 to 3V
2023-04-19 Give more clues about IMU CS
2023-04-19 new example for lsm6dS0
2023-04-19 clarify field names
2023-04-25 add more information about LED brightness.
2023-04-26 add instructions for checkout
2023-04-26 update requirements.
2023-05-01 Remove confusing LED driver description.
2023-05-08 typos and clarifications
2023-05-10 Adding parenthesis to CP equation.
2023-09-13 Slides as of the end of Spring 2023
2023-09-13 use correct prebuilts
2023-09-28 github classroom link
2023-09-30 ADd note about Fusion360 problems.
2023-09-30 Fix image reference in README
2023-10-02 restore slides
2023-10-03 typo.
2023-10-04 Update README.md
    Remove design review
2023-10-04 clarify hole placement.
2023-10-10 adjust for FA23
2023-11-28 replace readme
2024-09-26 New github classroom link
2024-10-08 Some changes for hardware lab
2024-10-08 new link
2024-10-08 assignment url.
2024-10-08 Updates near start of Fa2024
2024-10-08 Relabel layers
2024-10-17 Update README.md
    Antenna variant name.
2024-10-17 Update README.md
    fix gyro filter instructions.
2024-10-17 Update README.md
    remove tag requirement
2024-10-29 Change board layout trace width based on new Fusion360 version
2024-10-31 Change fanout instruction
2024-11-02 new slides and cam file
2024-11-07 clarify accelerameter config
2024-11-07 Clarify not to call quad_remote_setup() on the quad.
2024-12-11 Update Flashing-The-Bootloader.md
    remove obsolete command line option
